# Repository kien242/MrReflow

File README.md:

# ESPReflow
Firmware for SMT reflow controller.

> **!!! WARNING: This project deals with mains power and high current !!!**
> Please be careful if you wish to replicate any of it's functionality and never work on a PCB or any open wires that are connected to the mains !
> Author has no responsibility for your safety and wellbeing, so please take care of yourself.

This is a simplified version of the original one from https://github.com/foxis/ESPReflow,
it uses the simpler jquery webfrontend, a normal 3d printer thermistor and no additional IO chip, also the pcb integrates a small powersupply to allow direct wiring into the oven

## Modes of operation
### Reflow

In this mode the controller will perform reflow algorithm following selected reflow profile.
Controller will turn off the mode once the temperature reaches safe values after the profile is completed.

### Calibrate

In this mode a selected calibration algorithm will be used to find optimal PID controller parameters.
Controller will turn off the mode once the temperature reaches safe values after the calibration is completed.

### Keep Target

In this mode the controller will reach and maintain target temperature. Useful to check PID configuration. `default` PID configuration will be used in this mode.

# Flashing

There are two ways to flash the controller - via serial or via OTA.

## Serial

Find `RX/TX/GND` pins on the board, connect your serial adapter and flash either Arduino, PlatformIO or whatever flasher you like.
**NOTE: `RX/TX` pins are NOT 5V tolerant. Please use 3.3V serial adapter or level shifter from 5V**

## OTA

When the controller is first turned on it creates an AP with the name `ESPReflow` and the ip address `192.168.4.1`. Connect to the controller, wait until the page loads and go to `Setup`, enter WiFi SSID and credentials. Save the configuration and reboot.
After this is done it will connect to the specified WiFi AP and will register it's own domain as `ReflowControl.local`.
Tuning and operation of the controller can then be done.

## OTA HTTP upload

You can upload a firmware binary using `Setup` - just upload the new firmware on the WebUI.

# Usage

## Connect your hotplate/oven

### Hot plate

### IR Hot plate

## K-type thermal probe

Thermocouple must be placed on a dummy board, that would approximately resemble the target boards. For best results that board must be placed in a similar matter as the target board. Furthermore, since hotplates do not heat evenly(even some ovens), care must be taken to allow dummy board be heated the same way as the target board(i.e. it must be placed approximately the same distance and orientation as the target board in respect to the heating elements). Otherwise you may burn the target board.

## PID tuning

PID tuning must be done for every heating device individually. You can do it by trial and error, or ESPReflow can do it for you. There are several auto tuning algorithms available (a slightly modified [PID-aTune library fork](https://github.com/t0mpr1c3/Arduino-PID-AutoTune-Library)):

*		ZIEGLER_NICHOLS_PI
*		ZIEGLER_NICHOLS_PID
*		TYREUS_LUYBEN_PI
*		TYREUS_LUYBEN_PID
*		CIANCONE_MARLIN_PI
*		CIANCONE_MARLIN_PID
*		AMIGOF_PI
*		PESSEN_INTEGRAL_PID
*		SOME_OVERSHOOT_PID
*		NO_OVERSHOOT_PID"

## Reflow profile

# Problem Solving

## Unable to properly tune IR Hot plate

During development a cheap IR hot plate was used. I found that if you place your temperature probe and the boards on the hot plate itself it would be very hard to control the temperature of the board properly. So, I used aluminium raisers, that raise the board around 5-10mm from the hot plate so that IR radiation would heat the boards instead of the glass plate.

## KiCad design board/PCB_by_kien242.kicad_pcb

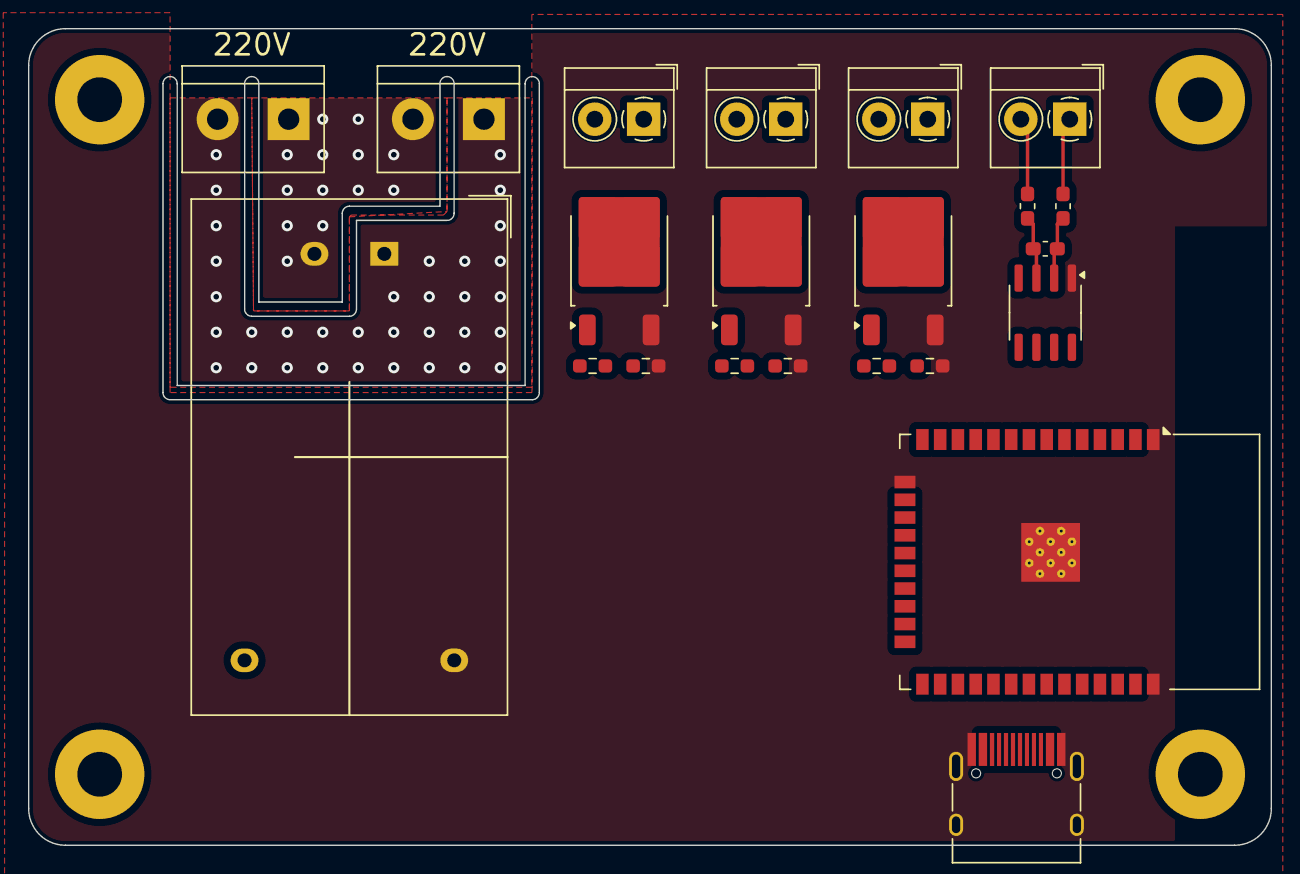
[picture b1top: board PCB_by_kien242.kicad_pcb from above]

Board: 2 copper layers, 88.9 x 58.4 mm, 26 parts (0 on the bottom side), 24 nets.

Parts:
C11: 10n; C_0603_1608Metric_Pad1.08x0.95mm_HandSolder
H1, H2, H3, H4: MountingHole_Pad; MountingHole_3.2mm_M3_Pad
J1, J3: VIN; TerminalBlock_bornier-2_P5.08mm
J2: USB-C-16pin-hight-v2
J4: TC1; TerminalBlock_4Ucon_1x02_P3.50mm_Horizontal
J6: SSR1; TerminalBlock_4Ucon_1x02_P3.50mm_Horizontal
J7: SSR2; TerminalBlock_4Ucon_1x02_P3.50mm_Horizontal
J8: SSR3; TerminalBlock_4Ucon_1x02_P3.50mm_Horizontal
L1, L2: ferrite; L_0603_1608Metric_Pad1.05x0.95mm_HandSolder
PS1: HLK-PM05; Converter_ACDC_Hi-Link_HLK-PMxx
Q4, Q5, Q6: IRLR2905Z; TO-252-2
R19, R20: R_Small; R_0603_1608Metric_Pad0.98x0.95mm_HandSolder
R21: ??; R_0603_1608Metric_Pad0.98x0.95mm_HandSolder
R22, R23, R24: 10k; R_0603_1608Metric_Pad0.98x0.95mm_HandSolder
U4: MAX31855KASA; SOIC-8_3.9x4.9mm_P1.27mm
U5: ESP32-WROOM-32

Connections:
+3.3V: U4.4 (VCC), U5.2 (VDD)
CS0: U4.6 (~CS), U5.23 (IO15)
D+: J2.A6 (D+), J2.B6 (D+)
D-: J2.A7 (D-), J2.B7 (D-)
GND: J2.A1 (GND), J2.A12 (GND), J2.B1 (GND), J2.B12 (GND), J2.S1 (SHIELD), PS1.3 (-Vout), Q4.3 (S), Q5.3 (S), Q6.3 (S), R22.2, R23.2, R24.2, U4.1 (GND), U5.1 (GND), U5.15 (GND), U5.38 (GND), U5.39 (GND)
MISO: U4.7 (SO), U5.14 (IO12)
unnamed: J1.1, J3.2, PS1.1 (AC/L)
unnamed: J1.2, J3.1, PS1.2 (AC/N)
unnamed: J4.1, L2.2
unnamed: J4.2, L1.2
unnamed: J6.1, Q4.2 (D)
unnamed: J7.1, Q5.2 (D)
unnamed: J8.1, Q6.2 (D)
unnamed: Q4.1 (G), R19.2
unnamed: Q5.1 (G), R20.2
unnamed: Q6.1 (G), R21.2
unnamed: C11.1, L1.1, U4.3 (T+)
unnamed: C11.2, L2.1, U4.2 (T-)
SCK: U4.5 (SCK), U5.13 (IO14)
SSR1: R21.1, R24.1, U5.10 (IO25)
SSR2: R20.1, R23.1, U5.11 (IO26)
SSR3: R19.1, R22.1, U5.12 (IO27)
VBUS: J2.A4 (VBUS), J2.A9 (VBUS), J2.B4 (VBUS), J2.B9 (VBUS)
V_SSR: J6.2, J7.2, J8.2, PS1.4 (+Vout)

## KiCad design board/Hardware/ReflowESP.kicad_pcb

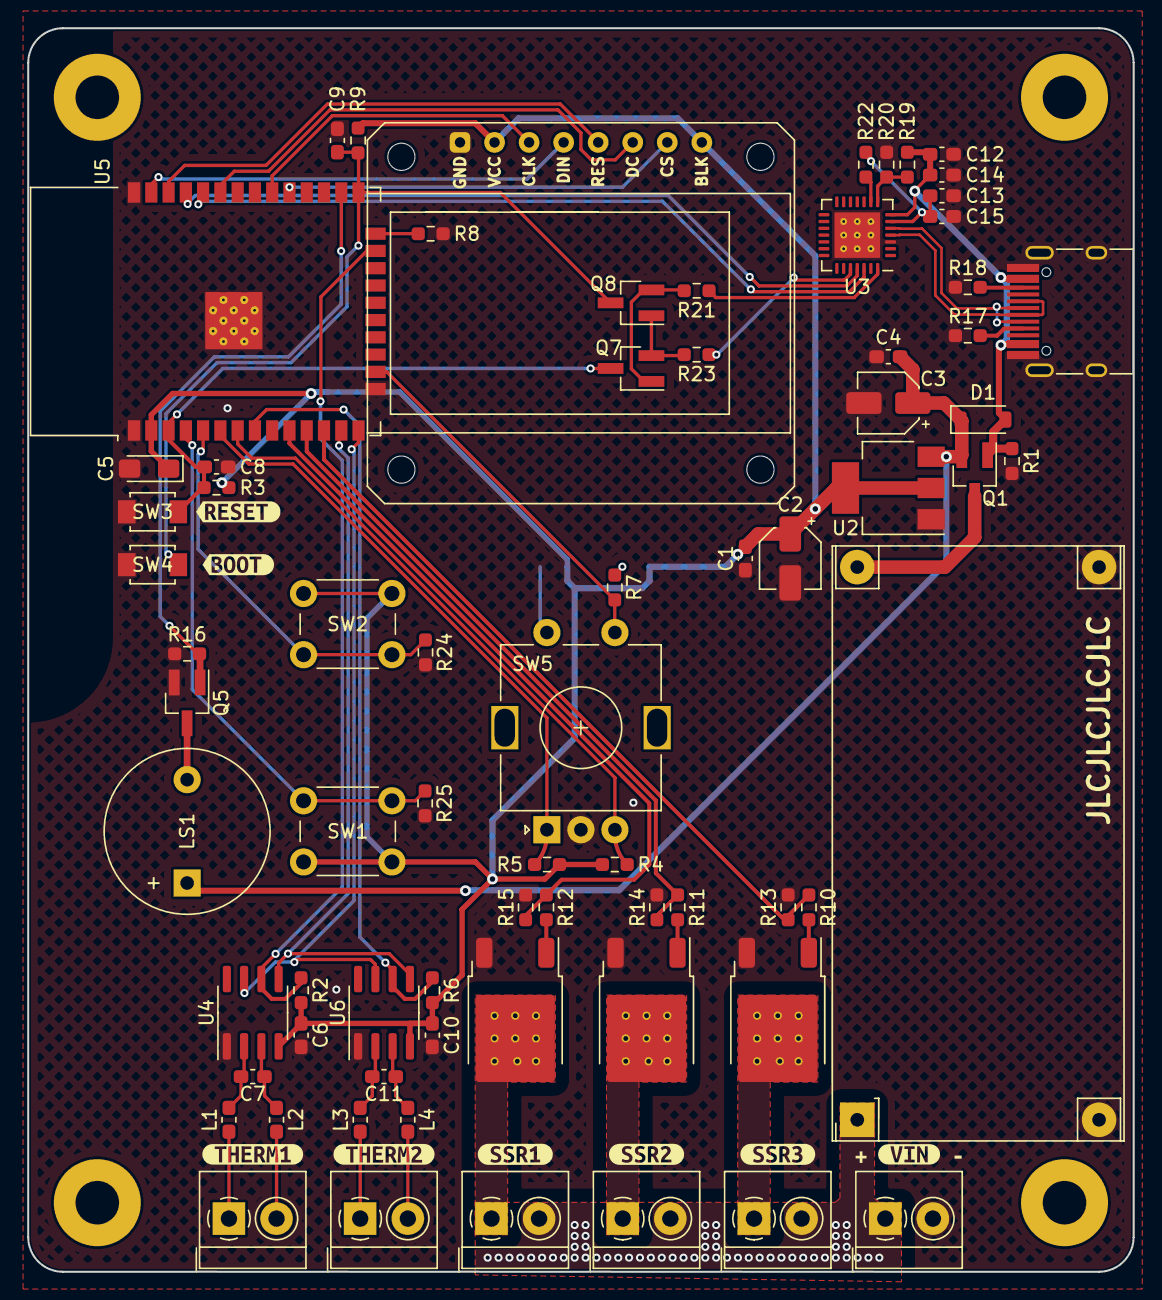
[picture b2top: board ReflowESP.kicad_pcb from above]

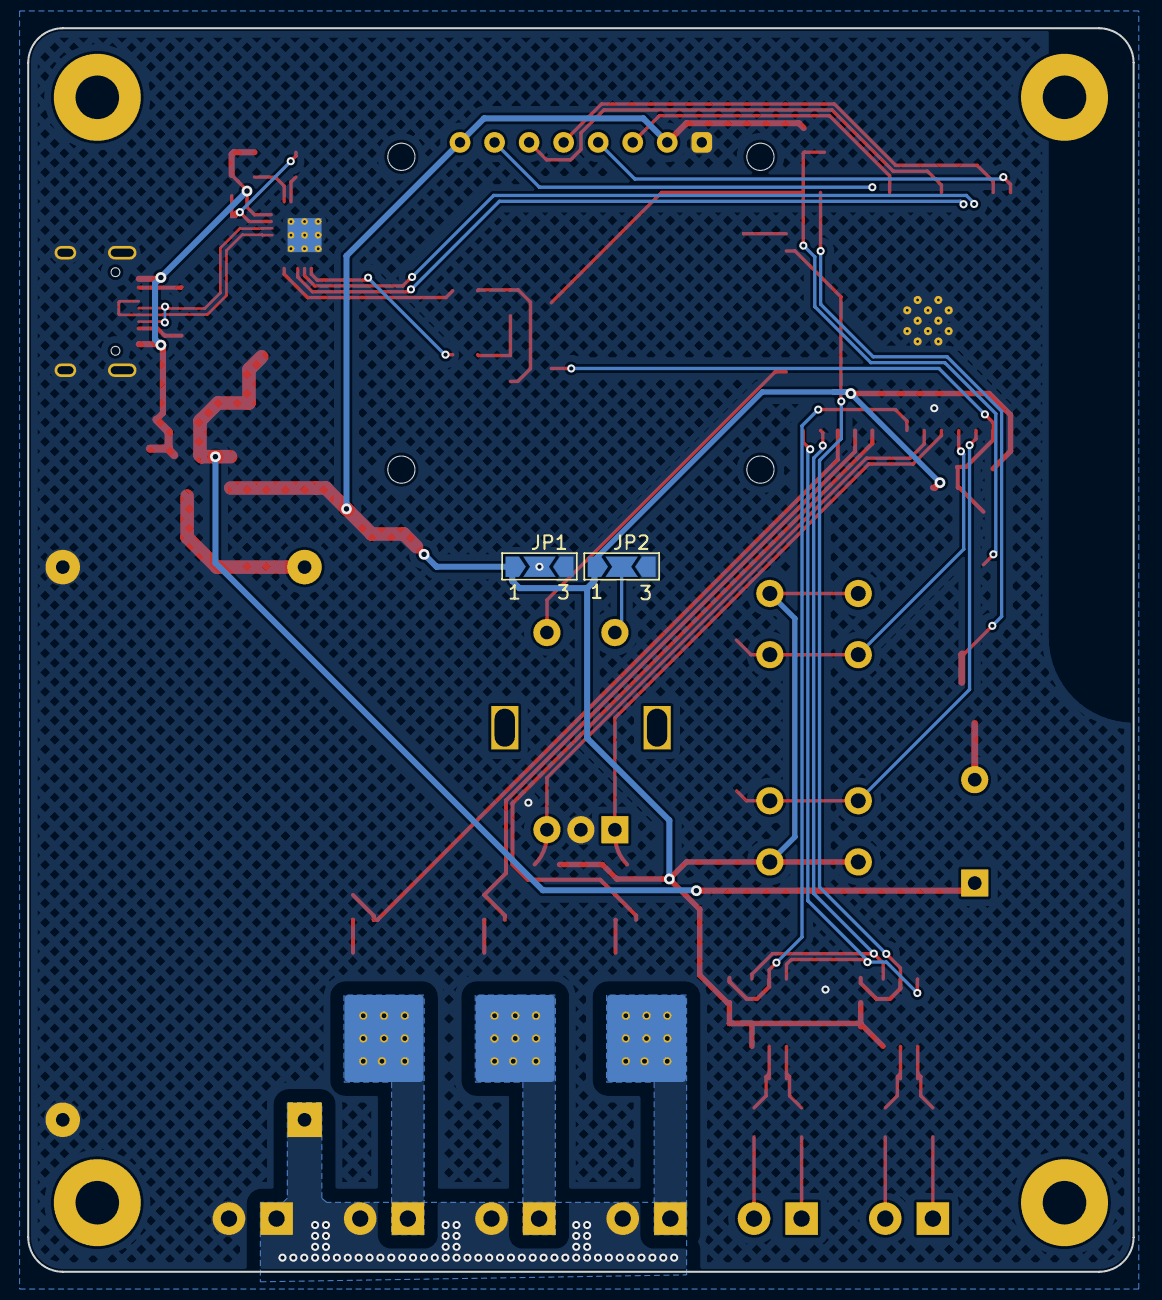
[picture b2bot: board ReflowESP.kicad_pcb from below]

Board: 2 copper layers, 81.3 x 91.4 mm, 88 parts (2 on the bottom side), 57 nets.

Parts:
C1, C4: 1u; C_0603_1608Metric_Pad1.08x0.95mm_HandSolder
C2, C3: 10u; CP_Elec_4x5.4
C5: CP_EIA-3216-12_Kemet-S_Pad1.58x1.35mm_HandSolder
C6, C8, C9, C10: 100n; C_0603_1608Metric_Pad1.08x0.95mm_HandSolder
C7, C11: 10n; C_0603_1608Metric_Pad1.08x0.95mm_HandSolder
C12, C15: 10uF; C_0603_1608Metric_Pad1.08x0.95mm_HandSolder
C13, C14: 100nF; C_0603_1608Metric_Pad1.08x0.95mm_HandSolder
D1: 1N5819; D_SOD-123
H1, H2, H3, H4: MountingHole_Pad; MountingHole_3.2mm_M3_Pad
J1: VIN; TerminalBlock_4Ucon_1x02_P3.50mm_Horizontal
J2: USB-C-16pin-hight-v2
J3: Conn_01x08; 1.14_TFT_Display
J4: TC1; TerminalBlock_4Ucon_1x02_P3.50mm_Horizontal
J5: TC2; TerminalBlock_4Ucon_1x02_P3.50mm_Horizontal
J6: SSR1; TerminalBlock_4Ucon_1x02_P3.50mm_Horizontal
J7: SSR2; TerminalBlock_4Ucon_1x02_P3.50mm_Horizontal
J8: SSR3; TerminalBlock_4Ucon_1x02_P3.50mm_Horizontal
JP1, JP2: SolderJumper-3_P2.0mm_Open_TrianglePad1.0x1.5mm_NumberLabels
L1, L2, L3, L4: ferrite; L_0603_1608Metric_Pad1.05x0.95mm_HandSolder
LS1: Speaker; Buzzer_12x9.5RM7.6
Q1: AO3407; SOT-23_Handsoldering
Q2, Q3, Q4: IRLR2905Z; TO-252-2
Q5: BSS138; SOT-23_Handsoldering
Q7, Q8: 2N3904; SOT-23_Handsoldering
R1: 100K; R_0603_1608Metric_Pad0.98x0.95mm_HandSolder
R2, R3, R4, R5, R6, R7, R13, R14, R15, R16, R24, R25: 10k; R_0603_1608Metric_Pad0.98x0.95mm_HandSolder
R8, R9: 5k; R_0603_1608Metric_Pad0.98x0.95mm_HandSolder
R10, R11: R_Small; R_0603_1608Metric_Pad0.98x0.95mm_HandSolder
R12: ??; R_0603_1608Metric_Pad0.98x0.95mm_HandSolder
R17, R18: 5k1; R_0603_1608Metric_Pad0.98x0.95mm_HandSolder
R19: 22k1; R_0603_1608Metric_Pad0.98x0.95mm_HandSolder
R20: 47k5; R_0603_1608Metric_Pad0.98x0.95mm_HandSolder
R21, R23: 22r; R_0603_1608Metric_Pad0.98x0.95mm_HandSolder
R22: 1k; R_0603_1608Metric_Pad0.98x0.95mm_HandSolder
SW1, SW2: SW_PUSH_6mm_H13mm
SW3: SW_RESET; SW_SPST_B3U-1000P
SW4: SW_BOOT; SW_SPST_B3U-1000P
SW5: RotaryEncoder_Alps_EC11E-Switch_Vertical_H20mm
U1: YAAJ_DCDC_StepDown_LM2596
U2: NCP1117-3.3_SOT223; SOT-223-3_TabPin2
U3: CP2102-GM; QFN-28-1EP_5x5mm_P0.5mm_EP3.35x3.35mm_ThermalVias
U4, U6: MAX31855KASA; SOIC-8_3.9x4.9mm_P1.27mm
U5: ESP32-WROOM-32
kibuzzard-6465B1A6: G***; kibuzzard-6465B1A6
kibuzzard-6465B1D4: G***; kibuzzard-6465B1D4
kibuzzard-6465B1DF: G***; kibuzzard-6465B1DF
kibuzzard-6465FE6A: G***; kibuzzard-6465FE6A
kibuzzard-6465FE70: G***; kibuzzard-6465FE70
kibuzzard-64660A1B: G***; kibuzzard-64660A1B
kibuzzard-64660A10: G***; kibuzzard-64660A10
kibuzzard-64660AB6: G***; kibuzzard-64660AB6
kibuzzard-64660ABC: G***; kibuzzard-64660ABC
kibuzzard-646609E4: G***; kibuzzard-646609E4

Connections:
+3.3V: C1.2, C2.1, C5.1, C6.1, C10.1, J3.2, J3.8, JP1.1 (A), JP2.1 (A), R2.2, R3.1, R4.1, R5.2, R6.2, R9.1, SW1.2, SW2.1, U2.2 (VO), U4.4 (VCC), U5.2 (VDD), U6.4 (VCC)
+5V: C3.1, C4.2, D1.1 (K), LS1.1, Q1.2 (S), U2.3 (VI)
BUZZER: Q5.1 (G), R16.2, U5.26 (IO4)
CS0: R2.1, U4.6 (~CS), U5.23 (IO15)
CS1: R6.1, U5.8 (IO32), U6.6 (~CS)
D+: J2.A6 (D+), J2.B6 (D+), U3.4 (D+)
D-: J2.A7 (D-), J2.B7 (D-), U3.5 (D–)
DC: J3.6, U5.33 (IO21)
DTR: R21.1, U3.28 (~DTR)
EN: C8.1, Q7.3 (C), R3.2, SW3.2, U5.3 (EN)
GND: C1.1, C2.2, C3.2, C4.1, C5.2, C6.2, C8.2, C9.2, C10.2, C12.1, C13.2, C14.2, C15.1, J1.2, J2.A1 (GND), J2.A12 (GND), J2.B1 (GND), J2.B12 (GND), J2.S1 (SHIELD), J3.1, JP1.3 (B), JP2.3 (B), Q2.3 (S), Q3.3 (S), Q4.3 (S), Q5.2 (S), R1.2, R8.2, R13.2, R14.2, R15.2, R16.1, R17.1, R18.1, R20.2, R24.2, R25.2, SW3.1, SW4.1, SW5.C, U1.2 (GND), U1.3 (GND), U2.1 (GND), U3.3 (GND), U3.29 (GND), U4.1 (GND), U5.1 (GND), U5.15 (GND), U5.38 (GND), U5.39 (GND), U6.1 (GND)
IO0: C9.1, Q8.3 (C), R9.2, SW4.2, U5.25 (IO0)
IO2: R8.1, U5.24 (IO2)
MISO: U4.7 (SO), U5.14 (IO12), U6.7 (SO)
unnamed: J2.A5 (CC1), R17.2
unnamed: J2.B5 (CC2), R18.2
unnamed: J4.1, L1.1
unnamed: J4.2, L2.2
unnamed: J5.1, L3.1
unnamed: J5.2, L4.2
unnamed: J6.1, Q2.2 (D)
unnamed: J7.1, Q3.2 (D)
unnamed: J8.1, Q4.2 (D)
unnamed: JP1.2 (C), R7.1
unnamed: JP2.2 (C), SW5.S1
unnamed: Q1.3 (D), U1.4 (Vout)
unnamed: Q2.1 (G), R10.2
unnamed: Q3.1 (G), R11.2
unnamed: Q4.1 (G), R12.2
unnamed: LS1.2, Q5.3 (D)
unnamed: Q7.1 (B), Q8.2 (E), R21.2
unnamed: Q7.2 (E), Q8.1 (B), R23.2
unnamed: R22.2, U3.9 (~RST)
unnamed: C7.1, L2.1, U4.3 (T+)
unnamed: C7.2, L1.2, U4.2 (T-)
unnamed: C11.1, L4.1, U6.3 (T+)
unnamed: C11.2, L3.2, U6.2 (T-)
RE_A: R5.1, SW5.A, U5.6 (IO34)
RE_B: R4.2, SW5.B, U5.7 (IO35)
RE_SW: R7.2, SW5.S2, U5.16 (IO13)
RST: J3.5, U5.36 (IO22)
RTS: R23.1, U3.24 (~RTS)
RX: U3.26 (TXD), U5.34 (RXD0/IO3)
SCK: U4.5 (SCK), U5.13 (IO14), U6.5 (SCK)
SSR1: R12.1, R15.1, U5.10 (IO25)
SSR2: R11.1, R14.1, U5.11 (IO26)
SSR3: R10.1, R13.1, U5.12 (IO27)
SW_1: R25.1, SW1.1, U5.4 (SENSOR_VP)
SW_2: R24.1, SW2.2, U5.5 (SENSOR_VN)
TX: U3.25 (RXD), U5.35 (TXD0/IO1)
VBUS: C12.2, C14.1, D1.2 (A), J2.A4 (VBUS), J2.A9 (VBUS), J2.B4 (VBUS), J2.B9 (VBUS), Q1.1 (G), R1.1, R19.1, U3.7 (REGIN)
VBUSREF: R19.2, R20.1, U3.8 (VBUS)
VCC: C13.1, C15.2, R22.1, U3.6 (VDD)
V_CS0: J3.7, U5.29 (IO5)
V_MOSI: J3.4, U5.37 (IO23)
V_SCK: J3.3, U5.30 (IO18)
V_SSR: J1.1, J6.2, J7.2, J8.2, U1.1 (Vin)

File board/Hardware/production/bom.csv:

Designator,Footprint,Quantity,Value,LCSC Part #
"C1, C4",0603,2,1u,
"C10, C6, C8, C9",0603,4,100n,
"C11, C7",0603,2,10n,
"C12, C15",0603,2,10uF,
"C13, C14",0603,2,100nF,
"C2, C3",CP_Elec_4x5.4,2,10u,
C5,CP_EIA-3216-12_Kemet-S_Pad1.58x1.35mm_HandSolder,1, ,
D1,D_SOD-123,1,1N5819,
"H1, H2, H3, H4",MountingHole_3.2mm_M3_Pad,4,MountingHole_Pad,
J1,TerminalBlock_4Ucon_1x02_P3.50mm_Horizontal,1,VIN,
J2,USB-C-16pin-hight-v2,1, ,
J3,1.14_TFT_Display,1,Conn_01x08,
J4,TerminalBlock_4Ucon_1x02_P3.50mm_Horizontal,1,TC1,
J5,TerminalBlock_4Ucon_1x02_P3.50mm_Horizontal,1,TC2,
J6,TerminalBlock_4Ucon_1x02_P3.50mm_Horizontal,1,SSR1,
J7,TerminalBlock_4Ucon_1x02_P3.50mm_Horizontal,1,SSR2,
J8,TerminalBlock_4Ucon_1x02_P3.50mm_Horizontal,1,SSR3,
"JP1, JP2",SolderJumper-3_P2.0mm_Open_TrianglePad1.0x1.5mm_NumberLabels,2, ,
"L1, L2, L3, L4",0603,4,ferrite,
LS1,Buzzer_12x9.5RM7.6,1,Speaker,
Q1,SOT-23_Handsoldering,1,AO3407,
"Q2, Q3, Q4",TO-252-2,3,IRLR2905Z,
Q5,SOT-23_Handsoldering,1,BSS138,
"Q7, Q8",SOT-23_Handsoldering,2,2N3904,
R1,0603,1,100K,
"R10, R11",0603,2,R_Small,
R12,0603,1,??,
"R13, R14, R15, R16, R2, R24, R25, R3, R4, R5, R6, R7",0603,12,10k,
"R17, R18",0603,2,5k1,
R19,0603,1,22k1,
R20,0603,1,47k5,
"R21, R23",0603,2,22r,
R22,0603,1,1k,
"R8, R9",0603,2,5k,
"SW1, SW2",SW_PUSH_6mm_H13mm,2, ,
SW3,SW_SPST_B3U-1000P,1,SW_RESET,
SW4,SW_SPST_B3U-1000P,1,SW_BOOT,
SW5,RotaryEncoder_Alps_EC11E-Switch_Vertical_H20mm,1, ,
U1,YAAJ_DCDC_StepDown_LM2596,1,YAAJ_DCDC_StepDown_LM2596,
U2,SOT-223-3_TabPin2,1,NCP1117-3.3_SOT223,
U3,QFN-28-1EP_5x5mm_P0.5mm_EP3.35x3.35mm_ThermalVias,1,CP2102-GM,
"U4, U6",SOIC-8_3.9x4.9mm_P1.27mm,2,MAX31855KASA,
U5,ESP32-WROOM-32,1,ESP32-WROOM-32,

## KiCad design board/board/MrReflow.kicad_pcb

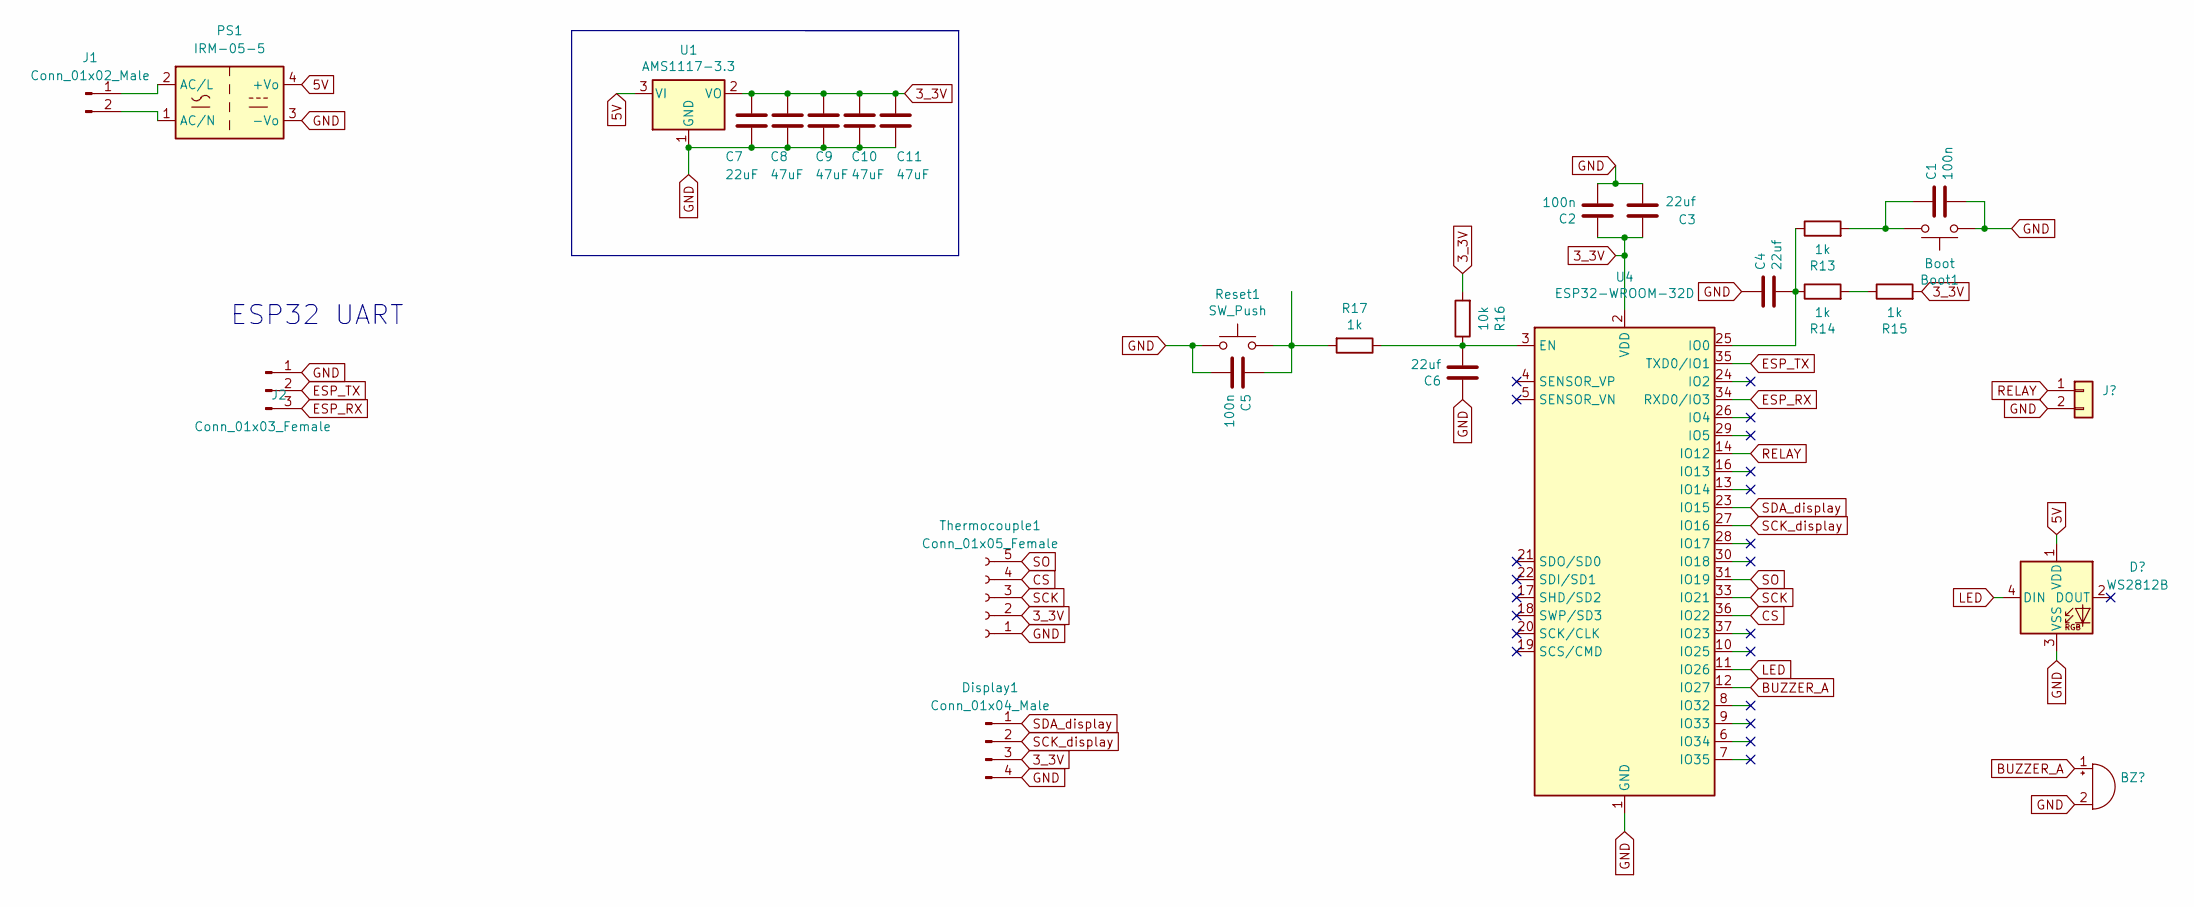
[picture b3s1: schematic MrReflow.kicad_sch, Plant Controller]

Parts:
Boot1: Boot; SW_SPST_CK_RS282G05A3; LCSC_PART_NUMBER C72443
C1, C2, C5: 100n; C_0805_2012Metric; LCSC_PART_NUMBER C49678
C3, C4, C6: 22uf; C_0805_2012Metric; LCSC_PART_NUMBER C45783
C7: 22uF; C_0603_1608Metric; LCSC C59461
C8, C9, C10, C11: 47uF; C_0805_2012Metric; LCSC C16780
Display1: Conn_01x04_Male; PinHeader_1x04_P2.54mm_Vertical
J1: Conn_01x02_Male; PhoenixContact_MSTBA_2,5_2-G-5,08_1x02_P5.08mm_Horizontal
J2: Conn_01x03_Female; PinHeader_1x03_P2.54mm_Vertical
PS1: IRM-05-5; Converter_ACDC_MeanWell_IRM-05-xx_THT
R13, R17: 1k; R_0805_2012Metric; LCSC_PART_NUMBER C95781
R14, R15: 1k; R_0805_2012Metric; LCSC_PART_NUMBER C212284
R16: 10k; R_0805_2012Metric; LCSC_PART_NUMBER C212284
Reset1: SW_Push; SW_SPST_CK_RS282G05A3; LCSC_PART_NUMBER C72443
Thermocouple1: Conn_01x05_Female; PinHeader_1x05_P2.54mm_Vertical
U1: AMS1117-3.3; SOT-223-3_TabPin2; LCSC C96123
U4: ESP32-WROOM-32D; ESP32-WROOM-32; LCSC_PART_NUMBER C529578

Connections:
3_3V: C2.2, C3.1, C7.1, C8.1, C9.1, C10.1, C11.1, Display1.3, R15.2, R16.2, Thermocouple1.2, U1.2 (VO), U4.2 (VDD)
5V: PS1.4 (+Vo), U1.3 (VI); also elsewhere on the board
BUZZER_A: U4.12 (IO27)
CS: Thermocouple1.4, U4.36 (IO22)
ESP_RX: J2.3, U4.34 (RXD0/IO3)
ESP_TX: J2.2, U4.35 (TXD0/IO1)
GND: Boot1.1, C1.1, C2.1, C3.2, C4.1, C5.1, C6.1, C7.2, C8.2, C9.2, C10.2, C11.2, Display1.4, J2.1, PS1.3 (-Vo), Reset1.1, Thermocouple1.1, U1.1 (GND), U4.1 (GND), U4.15 (GND), U4.38 (GND), U4.39 (GND); also elsewhere on the board
LED: U4.11 (IO26); also elsewhere on the board
unnamed: Boot1.2, C1.2, R13.2
unnamed: C4.2, R13.1, R14.1, U4.25 (IO0)
unnamed: C5.2, R17.2, Reset1.2
unnamed: C6.2, R16.1, R17.1, U4.3 (EN)
unnamed: J1.1, PS1.2 (AC/L)
unnamed: J1.2, PS1.1 (AC/N)
unnamed: R14.2, R15.1
RELAY: U4.14 (IO12)
SCK: Thermocouple1.3, U4.33 (IO21)
SCK_display: Display1.2, U4.27 (IO16)
SDA_display: Display1.1, U4.23 (IO15)
SO: Thermocouple1.5, U4.31 (IO19)

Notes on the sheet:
ESP32 UART

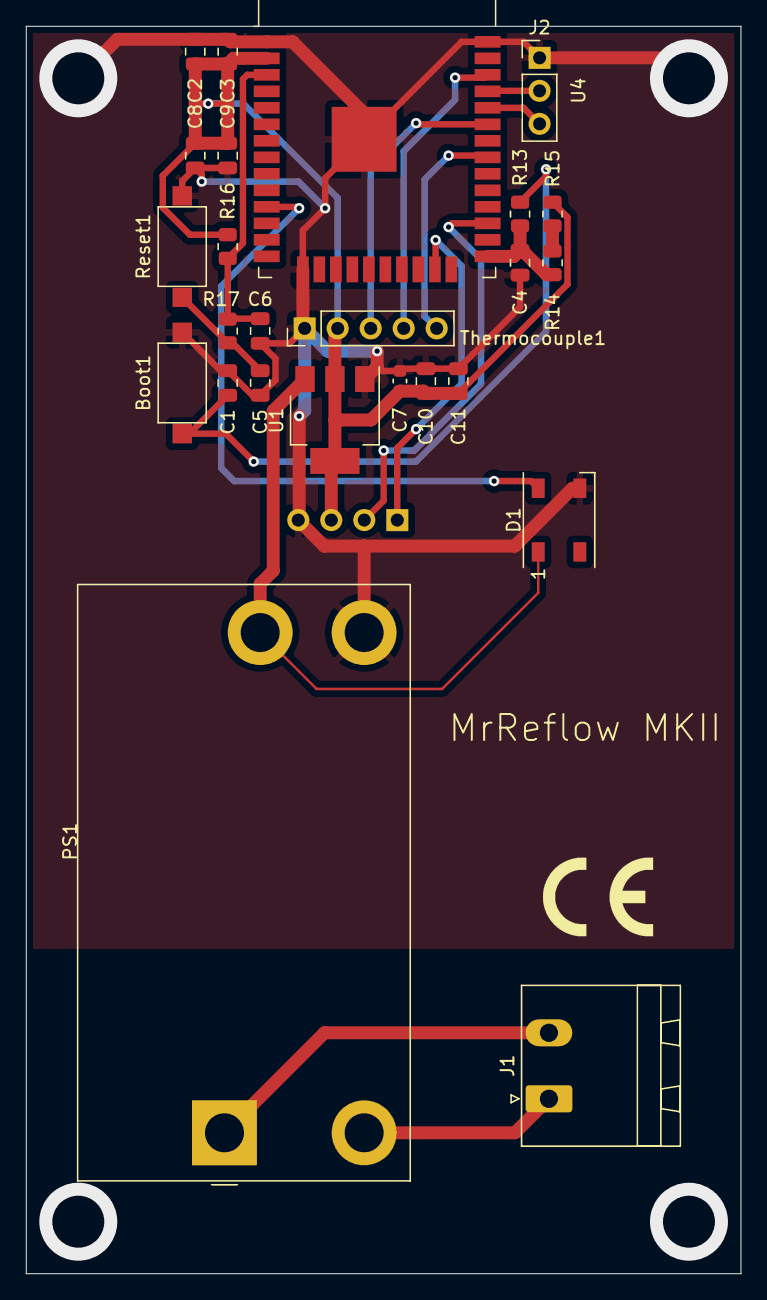
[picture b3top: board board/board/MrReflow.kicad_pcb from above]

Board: 2 copper layers, 55.0 x 96.0 mm, 26 parts (1 on the bottom side), 18 nets.

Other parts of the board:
D1: WS2812B; LED_WS2812B_PLCC4_5.0x5.0mm_P3.2mm

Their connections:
5V: D1.1 (VDD); also elsewhere on the board
GND: D1.3 (VSS); also elsewhere on the board
LED: D1.4 (DIN); also elsewhere on the board

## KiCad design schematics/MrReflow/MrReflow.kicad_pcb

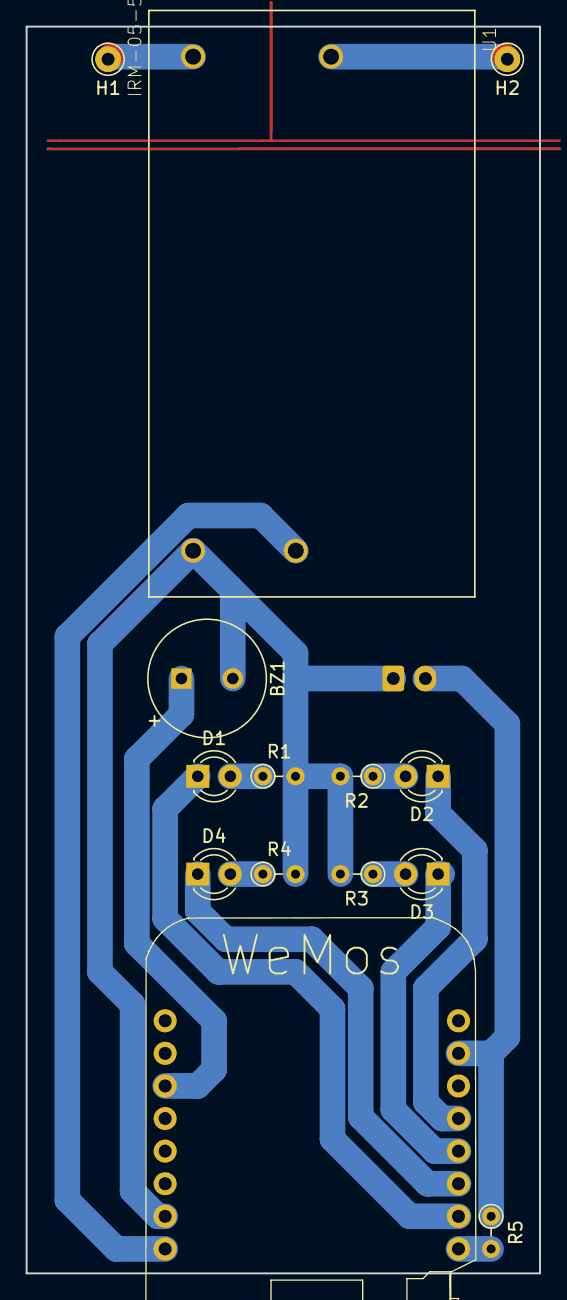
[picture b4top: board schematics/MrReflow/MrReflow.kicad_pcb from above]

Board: 2 copper layers, 40.0 x 97.2 mm, 15 parts (1 on the bottom side), 15 nets.

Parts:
BZ1: Buzzer; MagneticBuzzer_CUI_CST-931RP-A
D1: Yellow; LED_D3.0mm
D2: Green; LED_D3.0mm
D3: Blue; LED_D3.0mm
D4: Red; LED_D3.0mm
H1, H2: MountingHole_Pad; Pin_D1.0mm_L10.0mm
R1, R2, R3, R4: 470; R_Axial_DIN0204_L3.6mm_D1.6mm_P2.54mm_Vertical
R5: 100k; R_Axial_DIN0204_L3.6mm_D1.6mm_P2.54mm_Vertical
R6: T100k; JST_EH_B02B-EH-A_1x02_P2.50mm_Vertical
U1: IRM-05-5; CONV_IRM-05-5
U2: WeMos_mini; D1_mini_board

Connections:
unnamed: BZ1.1, U2.6
unnamed: BZ1.2, R1.2, R2.2, R3.2, R4.2, R6.1, U1.VNEG, U2.2
unnamed: D1.1, U2.15
unnamed: D1.2, R1.1
unnamed: D2.1, U2.12
unnamed: D2.2, R2.1
unnamed: D3.1, U2.13
unnamed: D3.2, R3.1
unnamed: D4.1, U2.14
unnamed: D4.2, R4.1
unnamed: H1.1, U1.AC/L
unnamed: H2.1, U1.AC/N
unnamed: R5.1, R6.2, U2.10
unnamed: R5.2, U2.16
unnamed: U1.VPOS, U2.1

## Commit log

2019-02-09 switched project to use simple thermistor and no io extender
2019-02-10 changed to older non npm webmodule
2019-02-10 removed unused webstuff
2019-02-10 removed OTA updates
2019-02-10 removed very spammy debug message
2019-02-10 configured ESP properly
2019-02-10 removed debugger statement, and fixed chart rendering
2019-02-10 buzzer check, pcb design
2019-02-10 layout adjustments
2019-02-10 converter command
2019-02-10 initial production run export
2019-02-10 initial production run
2019-02-10 removed ability to fuck up wlan config via wlan
2019-02-10 wlan status melodies
2019-02-20 fixed thermistor calibration
2019-02-20 added melodies
2019-02-20 They fixed the ld script, fixing our side for wemos flash
2019-02-20 use minified js again to fit default wemos flash
2019-02-20 some fixes
2019-03-01 Added recommended profiles for Sn63Pb37 (empire, 235C) and Sn42Bi57Ag1 (acid, 165C) pastes
2022-05-18 modernized pcb with esp32 modernized webapp
2023-05-16 Update file
2023-05-24 Update c_cpp_properties.json, MrReflow.kicad_prl, MrReflow.kicad_pro, and 3 more files
2023-06-16 Update c_cpp_properties.json, launch.json, settings.json, and 20 more files
2023-06-25 Update README.md, favicon.png, accept.png, and 64 more files
2023-08-21 Update c_cpp_properties.json, PCB_by_kien242.kicad_pcb, PCB_by_kien242.kicad_prl, and 155 more files
